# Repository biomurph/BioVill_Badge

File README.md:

# BioVill_Badge
DEFCON Micro Fluidics Badge Design For Biohacking Village

## Features Lifted From [OpenDrop](https://github.com/GaudiLabs/OpenDrop)V2
* Arduino Micro
* HV507 64 bit high voltage SIPO
* OLED display 
* Feedback circuit 
* Two pushbutton switches
* Joystick
* Speaker
* Various LEDs
* Various test points

## Power Supply	
Most important change from OpenDrop is the power supply. This board is asking to be plugged into the mains. Super important to isolate the grounds. Pay attention.

### Low voltage power supply sharing ground with USB 

* 5VDC supplied by USB connection to computer or battery on Vin
* 3V3 supplied by the Arduino Micro
		
### High voltage power supply sharing ground with high voltage input

* High voltage in to HV507

### High voltate input specs

* 110VAC <> 240VAC 50Hz <> 60Hz

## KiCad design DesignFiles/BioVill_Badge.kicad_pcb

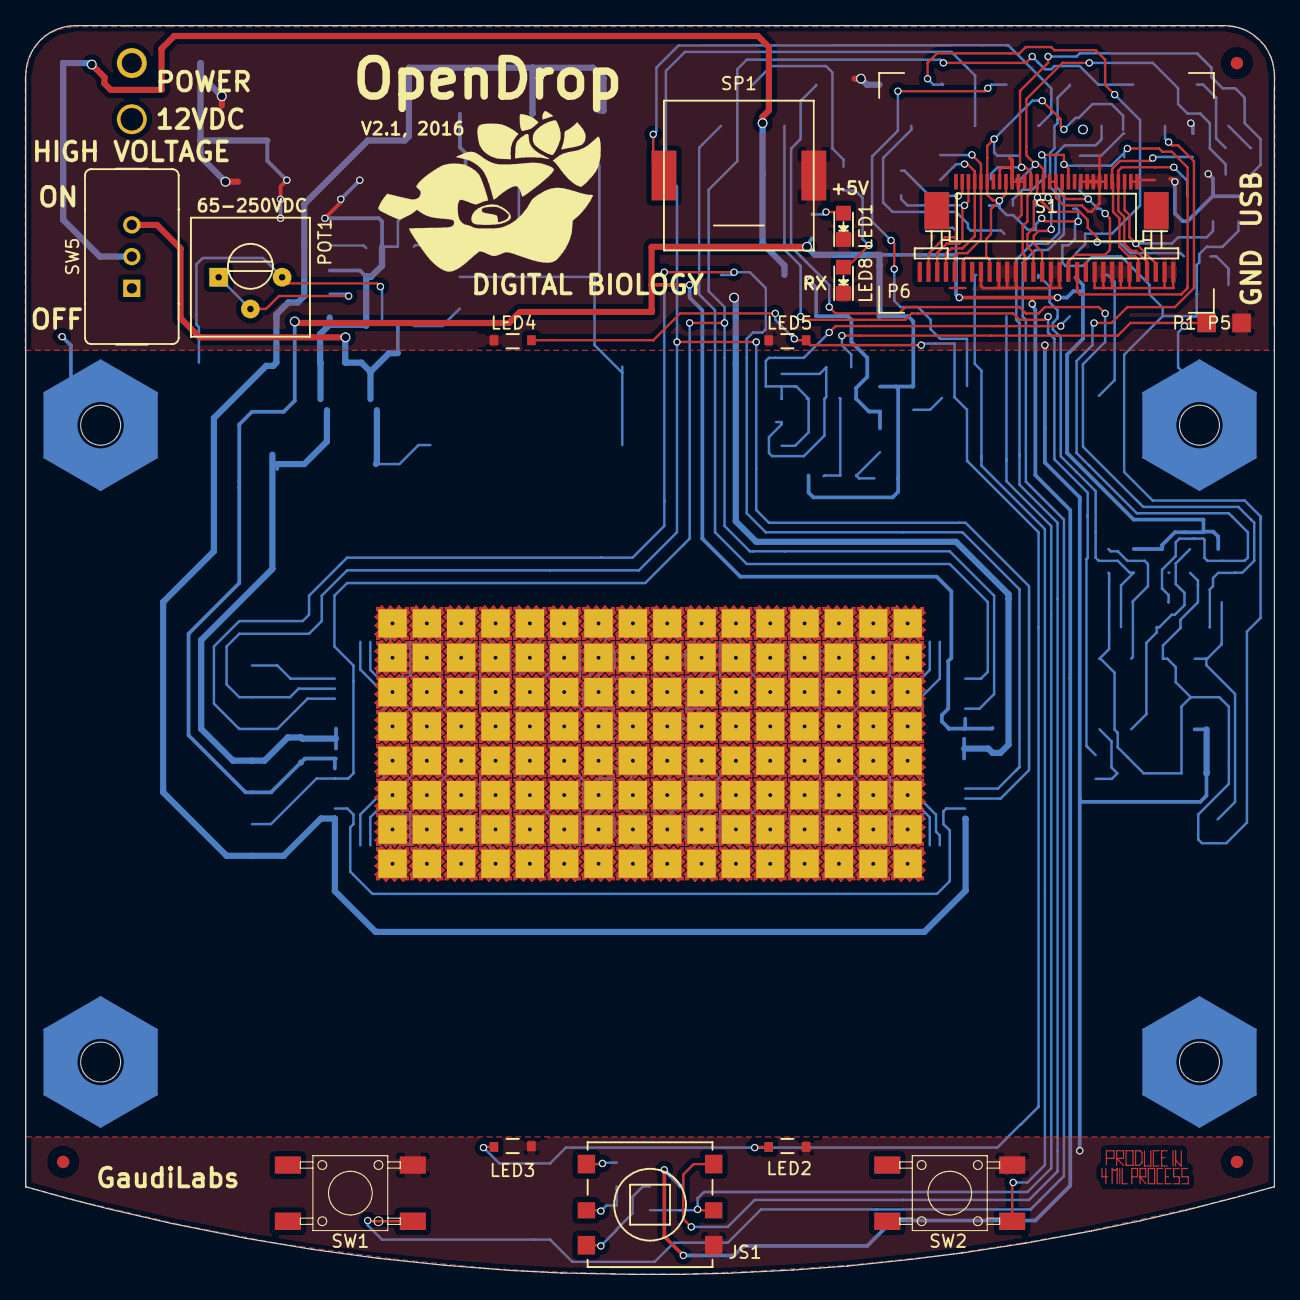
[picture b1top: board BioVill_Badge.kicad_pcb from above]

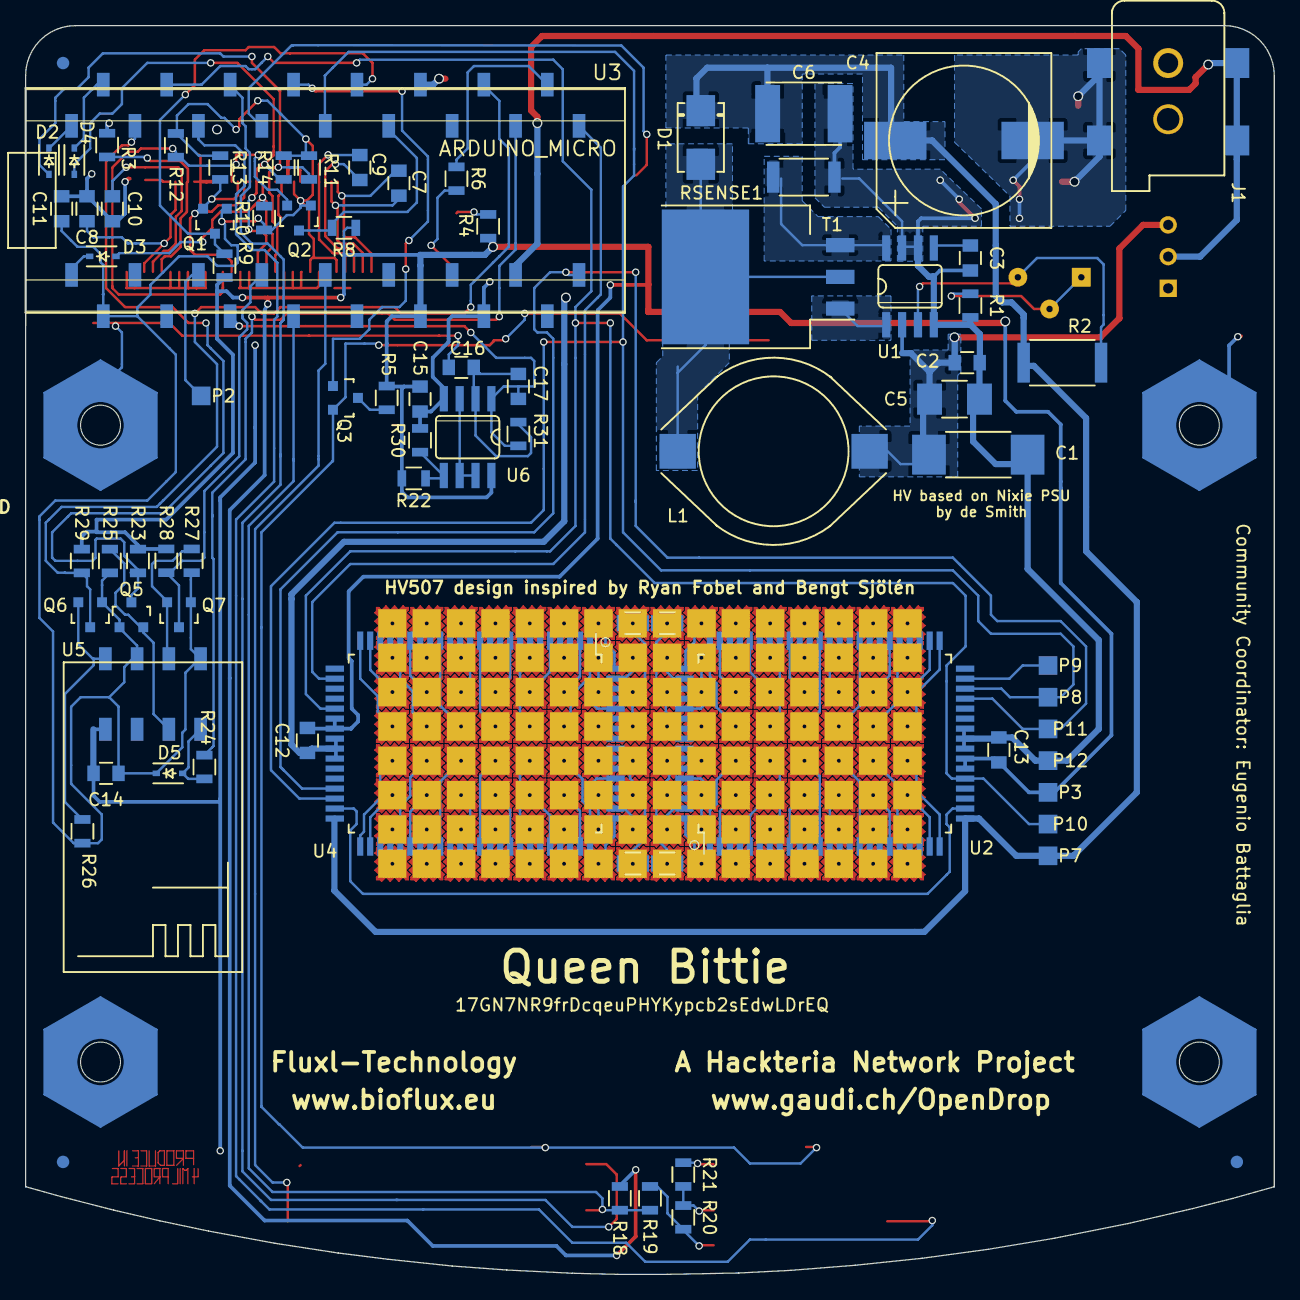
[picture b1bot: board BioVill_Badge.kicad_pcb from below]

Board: 2 copper layers, 100.0 x 100.0 mm, 225 parts (77 on the bottom side), 191 nets.

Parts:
C1: 100uF, 35V; R_2512_HandSoldering
C2, C3, C11, C12, C13, C14: 100nF; C_0805
C4: 4u7, 250V; C_SMD_12mm
C5: 10uF, 25V; C_1210_HandSoldering
C6: 100nF, 250V; C100n_250V
C7, C9, C15, C16: 1uF; C_0805
C8, C10: 2.2uF; C_0805
C17: 1pF; C_0805
D1: ES2F; DO-214AA
D2, D3, D4, D5: 1N4148; SOD-323
FLUXL1, FLUXL2, FLUXL3, FLUXL4, FLUXL5, FLUXL6, FLUXL7, FLUXL8, FLUXL9, FLUXL10, FLUXL11, FLUXL12, FLUXL13, FLUXL14, FLUXL15, FLUXL16, FLUXL17, FLUXL18, FLUXL19, FLUXL20, FLUXL21, FLUXL22, FLUXL23, FLUXL24, FLUXL25, FLUXL26, FLUXL27, FLUXL28, FLUXL29, FLUXL30, FLUXL31, FLUXL32, FLUXL33, FLUXL34, FLUXL35, FLUXL36, FLUXL37, FLUXL38, FLUXL39, FLUXL40, FLUXL41, FLUXL42, FLUXL43, FLUXL44, FLUXL45, FLUXL46, FLUXL47, FLUXL48, FLUXL49, FLUXL50, FLUXL51, FLUXL52, FLUXL53, FLUXL54, FLUXL55, FLUXL56, FLUXL57, FLUXL58, FLUXL59, FLUXL60, FLUXL61, FLUXL62, FLUXL63, FLUXL64, FLUXL65, FLUXL66, FLUXL67, FLUXL68, FLUXL69, FLUXL70, FLUXL71, FLUXL72, FLUXL73, FLUXL74, FLUXL75, FLUXL76, FLUXL77, FLUXL78, FLUXL79, FLUXL80, FLUXL81, FLUXL82, FLUXL83, FLUXL84, FLUXL85, FLUXL86, FLUXL87, FLUXL88, FLUXL89, FLUXL90, FLUXL91, FLUXL92, FLUXL93, FLUXL94, FLUXL95, FLUXL96, FLUXL97, FLUXL98, FLUXL99, FLUXL100, FLUXL101, FLUXL102, FLUXL103, FLUXL104, FLUXL105, FLUXL106, FLUXL107, FLUXL108, FLUXL109, FLUXL110, FLUXL111, FLUXL112, FLUXL113, FLUXL114, FLUXL115, FLUXL116, FLUXL117, FLUXL118, FLUXL119, FLUXL120, FLUXL121, FLUXL122, FLUXL123, FLUXL124, FLUXL125, FLUXL126, FLUXL127, FLUXL128: FX; FLUXPAD_2_75_4MIL_4_5
J1: DC_JACK; DC_JACK_SMD
JS1: JoystickSMD; JoystickSMD_SKQUSeries
L1: 100uH; Inductor_18.54x15.24
LED1, LED8: LED; LED-0805
LED2, LED3, LED4, LED5: LED; LED_SIDE
P1, P2, P3, P5, P7, P8, P9, P10, P11, P12: CONN_01X01; Measurement_Point_Square-SMD-Pad_Small
P6: CONN_01X30; OLED_SolderPads
P13, P13#2, P13#3, P13#4: ScrewPad1; MountingHolePad_3x9mm
POT1: 5k Ohm; Potentiometer_Trimmer-Suntan-TSR-3386P
Q1, Q2, Q3, Q5, Q6, Q7: BSS138; SOT-23
R1: 8k; R_0805
R2: 1M5; R_2512
R3: 390k; R_0805
R4, R6: 390; R_0805
R5: 10; R_0805
R7, R15, R16, R17: 10k; R_0805_HeatPad
R8, R9, R10, R11, R12, R13, R14, R18, R19, R20, R21, R22, R23, R24, R25, R26, R27, R28, R29, R30, R31: 10k; R_0805
RSENSE1: 0R050; R_2010
S1: OLED_DISPLAY; OLED_096_1
SP1: SPEAKER; SMD_PA12_Piezzo
SW1, SW2: SW_PUSH; PUSH_BUTTON_SMD
SW5: SPST; Switch_On-On
T1: IRF 840S; D2PAK
U1: MAX1771ESA; SO08
U2, U4: HV507; PQFP-80_14x20mm_Pitch0.8mm
U3: ARDUINO_MICRO; ARDUINO_MICRO_SMD
U5: ESP8266_SMD
U6: MCP6002; SO08

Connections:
3.3V: C11.1, C14.1, D5.1, P6.6, P6.9, Q1.1, Q2.1, Q5.1, Q6.1, Q7.1, R10.1, R11.1, R12.1, R13.1, R14.1, R25.2, R26.2, R27.2, S1.6, S1.9, U3.19, U5.4, U5.8
+5V: C12.1, C13.1, C15.1, P3.1, R4.1, R5.2, R8.1, R9.1, R18.2, R22.1, R23.2, R28.2, R29.2, U2.30, U2.31, U3.29, U4.30, U4.31, U6.8
BL: P10.1, U2.29, U3.14, U4.29
CLK: P11.1, U2.37, U3.34, U4.37
DI: U3.1, U4.26
DIO_B: P9.1, U2.39
DISP_CS: D2.1, U3.17
DISP_DC: D4.1, U3.16
DISP_RES: D3.1, U3.18
DISP_SCL: Q1.3, R9.2, U3.8
DISP_SDA: Q2.3, R8.2, U3.7
ESP_GPIO0: Q5.3, R23.1, U3.15
ESP_RESET: Q7.3, R28.1, U3.24
ESP_RX: R24.1, U3.3
ESP_TX: Q6.3, R29.1, U3.4
FEEDBACK: C17.1, R31.1, U3.23, U6.1
GND: C1.2, C2.2, C3.2, C4.2, C5.2, C6.2, C8.2, C10.2, C11.2, C12.2, C13.2, C14.2, C15.2, J1.1, J1.2, JS1.4, LED1.1, LED2.1, LED3.1, LED4.1, LED5.1, LED8.1, P5.1, P6.8, P6.10, P6.11, P6.12, P6.16, P6.17, P6.21, P6.22, P6.23, P6.24, P6.25, P6.29, P6.30, P12.1, R1.2, R3.2, R30.2, RSENSE1.2, S1.8, S1.10, S1.11, S1.12, S1.16, S1.17, S1.21, S1.22, S1.23, S1.24, S1.25, S1.29, S1.30, SP1.1, SW1.2, SW2.2, U1.4, U1.6, U1.7, U2.32, U2.33, U2.34, U3.6, U3.31, U4.32, U4.33, U4.34, U5.1, U6.4
JOY: JS1.5, R18.1, R19.2, U3.25
LE: P8.1, U2.38, U3.9, U4.38
LED_LIGHT: Q3.1, U3.10
unnamed: C1.1, C2.1, C5.1, L1.1, SW5.1, U1.2
unnamed: C3.1, U1.5
unnamed: C7.1, P6.2, S1.2
unnamed: C7.2, P6.3, S1.3
unnamed: C8.1, P6.28, S1.28
unnamed: C9.1, P6.4, S1.4
unnamed: C9.2, P6.5, S1.5
unnamed: C10.1, P6.27, S1.27
unnamed: C16.1, C17.2, R31.2, U6.2
unnamed: D1.2, L1.2, T1.2
unnamed: D2.2, P6.13, R11.2, S1.13
unnamed: D3.2, P6.14, R10.2, S1.14
unnamed: D4.2, P6.15, R14.2, S1.15
unnamed: D5.2, R24.2, U5.7
unnamed: FLUXL1.1, U2.44
unnamed: FLUXL2.1, U2.47
unnamed: FLUXL3.1, U2.51
unnamed: FLUXL4.1, U2.54
unnamed: FLUXL5.1, U2.58
unnamed: FLUXL6.1, U2.61
unnamed: FLUXL7.1, U2.65
unnamed: FLUXL8.1, U2.70
unnamed: FLUXL9.1, U2.43
unnamed: FLUXL10.1, U2.48
unnamed: FLUXL11.1, U2.50
unnamed: FLUXL12.1, U2.55
unnamed: FLUXL13.1, U2.59
unnamed: FLUXL14.1, U2.62
unnamed: FLUXL15.1, U2.69
unnamed: FLUXL16.1, U2.66
unnamed: FLUXL17.1, U2.42
unnamed: FLUXL18.1, U2.46
unnamed: FLUXL19.1, U2.52
unnamed: FLUXL20.1, U2.56
unnamed: FLUXL21.1, U2.60
unnamed: FLUXL22.1, U2.63
unnamed: FLUXL23.1, U2.68
unnamed: FLUXL24.1, U2.67
unnamed: FLUXL25.1, U2.41
unnamed: FLUXL26.1, U2.45
unnamed: FLUXL27.1, U2.49
unnamed: FLUXL28.1, U2.53
unnamed: FLUXL29.1, U2.57
unnamed: FLUXL30.1, U2.64
unnamed: FLUXL31.1, U2.72
unnamed: FLUXL32.1, U2.71
unnamed: FLUXL33.1, U2.24
unnamed: FLUXL34.1, U2.20
unnamed: FLUXL35.1, U2.16
unnamed: FLUXL36.1, U2.12
unnamed: FLUXL37.1, U2.8
unnamed: FLUXL38.1, U2.1
unnamed: FLUXL39.1, U2.73
unnamed: FLUXL40.1, U2.74
unnamed: FLUXL41.1, U2.23
unnamed: FLUXL42.1, U2.19
unnamed: FLUXL43.1, U2.13
unnamed: FLUXL44.1, U2.9
unnamed: FLUXL45.1, U2.5
unnamed: FLUXL46.1, U2.2
unnamed: FLUXL47.1, U2.78
unnamed: FLUXL48.1, U2.77
unnamed: FLUXL49.1, U2.22
unnamed: FLUXL50.1, U2.17
unnamed: FLUXL51.1, U2.15
unnamed: FLUXL52.1, U2.10
unnamed: FLUXL53.1, U2.6
unnamed: FLUXL54.1, U2.3
unnamed: FLUXL55.1, U2.76
unnamed: FLUXL56.1, U2.79
unnamed: FLUXL57.1, U2.21
unnamed: FLUXL58.1, U2.18
unnamed: FLUXL59.1, U2.14
unnamed: FLUXL60.1, U2.11
unnamed: FLUXL61.1, U2.7
unnamed: FLUXL62.1, U2.4
unnamed: FLUXL63.1, U2.80
unnamed: FLUXL64.1, U2.75
unnamed: FLUXL65.1, U4.41
unnamed: FLUXL66.1, U4.42
unnamed: FLUXL67.1, U4.43
unnamed: FLUXL68.1, U4.44
unnamed: FLUXL69.1, U4.45
unnamed: FLUXL70.1, U4.46
unnamed: FLUXL71.1, U4.47
unnamed: FLUXL72.1, U4.48
unnamed: FLUXL73.1, U4.49
unnamed: FLUXL74.1, U4.50
unnamed: FLUXL75.1, U4.51
unnamed: FLUXL76.1, U4.52
unnamed: FLUXL77.1, U4.53
unnamed: FLUXL78.1, U4.54
unnamed: FLUXL79.1, U4.55
unnamed: FLUXL80.1, U4.56
unnamed: FLUXL81.1, U4.57
unnamed: FLUXL82.1, U4.58
unnamed: FLUXL83.1, U4.59
unnamed: FLUXL84.1, U4.60
unnamed: FLUXL85.1, U4.61
unnamed: FLUXL86.1, U4.62
unnamed: FLUXL87.1, U4.63
unnamed: FLUXL88.1, U4.64
unnamed: FLUXL89.1, U4.65
unnamed: FLUXL90.1, U4.66
unnamed: FLUXL91.1, U4.67
unnamed: FLUXL92.1, U4.68
unnamed: FLUXL93.1, U4.69
unnamed: FLUXL94.1, U4.70
unnamed: FLUXL95.1, U4.71
unnamed: FLUXL96.1, U4.72
unnamed: FLUXL97.1, U4.73
unnamed: FLUXL98.1, U4.74
unnamed: FLUXL99.1, U4.75
unnamed: FLUXL100.1, U4.76
unnamed: FLUXL101.1, U4.77
unnamed: FLUXL102.1, U4.78
unnamed: FLUXL103.1, U4.79
unnamed: FLUXL104.1, U4.80
unnamed: FLUXL105.1, U4.1
unnamed: FLUXL106.1, U4.2
unnamed: FLUXL107.1, U4.3
unnamed: FLUXL108.1, U4.4
unnamed: FLUXL109.1, U4.5
unnamed: FLUXL110.1, U4.6
unnamed: FLUXL111.1, U4.7
unnamed: FLUXL112.1, U4.8
unnamed: FLUXL113.1, U4.9
unnamed: FLUXL114.1, U4.10
unnamed: FLUXL115.1, U4.11
unnamed: FLUXL116.1, U4.12
unnamed: FLUXL117.1, U4.13
unnamed: FLUXL118.1, U4.14
unnamed: FLUXL119.1, U4.15
unnamed: FLUXL120.1, U4.16
unnamed: FLUXL121.1, U4.17
unnamed: FLUXL122.1, U4.18
unnamed: FLUXL123.1, U4.19
unnamed: FLUXL124.1, U4.20
unnamed: FLUXL125.1, U4.21
unnamed: FLUXL126.1, U4.22
unnamed: FLUXL127.1, U4.23
unnamed: FLUXL128.1, U4.24
unnamed: JS1.1, R21.1
unnamed: JS1.2, R20.1, R21.2
unnamed: JS1.3, R19.1, R20.2
unnamed: LED1.2, R4.2
unnamed: LED2.2, LED3.2, LED4.2, LED5.2, Q3.2
unnamed: LED8.2, R6.2
unnamed: P2.1, U3.22
unnamed: P6.18, Q1.2, R13.2, S1.18
unnamed: P6.19, Q2.2, R12.2, S1.19
unnamed: P6.26, R3.1, S1.26
unnamed: POT1.1, POT1.2, R1.1
unnamed: POT1.3, R2.2, U1.3
unnamed: Q3.3, R5.1
unnamed: Q5.2, R25.1, U5.5
unnamed: Q6.2, R26.1, U5.2
unnamed: Q7.2, R27.1, U5.6
unnamed: R22.2, R30.1, U6.5
unnamed: RSENSE1.1, T1.3, U1.8
unnamed: T1.1, U1.1
unnamed: U2.26, U4.39
unnamed: U6.3, U6.6, U6.7
RX_LED: R6.1, U3.2
SPK: SP1.2, U3.11
SW1: SW1.1, U3.13
SW2: SW2.1, U3.26
SW3: JS1.6, U3.12
VIN: J1.3, SW5.2, U3.32
V_GND: C16.2, P1.1
V_HV: C4.1, C6.1, D1.1, P7.1, R2.1, U2.25, U4.40

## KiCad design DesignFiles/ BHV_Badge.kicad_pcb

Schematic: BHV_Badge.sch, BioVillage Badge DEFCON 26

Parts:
C1: 100uF, 35V; R_2512_HandSoldering
C2, C3, C12, C13, C14, C22, C26, C30, C33, C34, C36: 100nF; C_0805
C4, C18: 4u7, 250V; c_elec_10x10
C5, C21: 22uF; C_1206
C6, C35: 100nF, 250V; C_1206_HandSoldering
C7, C9, C11, C15, C16, C20, C24, C27: 1uF; C_0805
C8, C10: 2.2uF; C_0805
C17: 1pF; C_0805
C19: 22uF, 50V; c_elec_6.3x5.8
C23, C25: 22pF; C_0805
C28, C29: 3.3nF; C_0805
C31: 220nF; C_0805
C32: 100uF,50V; R_2512_HandSoldering
D1: ES2F; DO-214AA
D2, D3: 1N4148; D_SOD-323
FLUXL_1_1, FLUXL_1_8, FLUXL_16_1, FLUXL_16_8: FX; FLUXPAD_2_75_4MIL_4_5_res3
FLUXL_1_2, FLUXL_1_7, FLUXL_16_2, FLUXL_16_7: FX; FLUXPAD_2_75_4MIL_4_5_res1
FLUXL_1_3, FLUXL_1_6, FLUXL_16_3, FLUXL_16_6: FX; FLUXPAD_2_75_4MIL_4_5_res2
FLUXL_1_4, FLUXL_1_5, FLUXL_16_4, FLUXL_16_5: FX; FLUXPAD_2_75_4MIL_4_5_res4
FLUXL_1_4b1, FLUXL_1_5b1, FLUXL_16_4b1, FLUXL_16_5b1: FX; FLUXPAD_2_75_4MIL_4_5_res5
FLUXL_2_1, FLUXL_15_8: FX; FLUXPAD_2_75_4MIL_4_5_topleft
FLUXL_2_2, FLUXL_2_7, FLUXL_3_2, FLUXL_3_3, FLUXL_3_4, FLUXL_3_5, FLUXL_3_6, FLUXL_3_7, FLUXL_4_2, FLUXL_4_3, FLUXL_4_4, FLUXL_4_5, FLUXL_4_6, FLUXL_4_7, FLUXL_5_2, FLUXL_5_3, FLUXL_5_4, FLUXL_5_5, FLUXL_5_6, FLUXL_5_7, FLUXL_6_2, FLUXL_6_3, FLUXL_6_4, FLUXL_6_5, FLUXL_6_6, FLUXL_6_7, FLUXL_7_2, FLUXL_7_3, FLUXL_7_4, FLUXL_7_5, FLUXL_7_6, FLUXL_7_7, FLUXL_8_2, FLUXL_8_3, FLUXL_8_4, FLUXL_8_5, FLUXL_8_6, FLUXL_8_7, FLUXL_9_2, FLUXL_9_3, FLUXL_9_4, FLUXL_9_5, FLUXL_9_6, FLUXL_9_7, FLUXL_10_2, FLUXL_10_3, FLUXL_10_4, FLUXL_10_5, FLUXL_10_6, FLUXL_10_7, FLUXL_11_2, FLUXL_11_3, FLUXL_11_4, FLUXL_11_5, FLUXL_11_6, FLUXL_11_7, FLUXL_12_2, FLUXL_12_3, FLUXL_12_4, FLUXL_12_5, FLUXL_12_6, FLUXL_12_7, FLUXL_13_2, FLUXL_13_3, FLUXL_13_4, FLUXL_13_5, FLUXL_13_6, FLUXL_13_7, FLUXL_14_2, FLUXL_14_3, FLUXL_14_4, FLUXL_14_5, FLUXL_14_6, FLUXL_14_7, FLUXL_15_2, FLUXL_15_7: FX; FLUXPAD_2_75_4MIL_4_5
FLUXL_2_3, FLUXL_2_4, FLUXL_2_5, FLUXL_2_6, FLUXL_15_3, FLUXL_15_4, FLUXL_15_5, FLUXL_15_6: FX; FLUXPAD_2_75_4MIL_4_5_side
FLUXL_2_8, FLUXL_15_1: FX; FLUXPAD_2_75_4MIL_4_5_topright
FLUXL_3_1, FLUXL_3_8, FLUXL_4_1, FLUXL_4_8, FLUXL_5_1, FLUXL_5_8, FLUXL_6_1, FLUXL_6_8, FLUXL_7_1, FLUXL_7_8, FLUXL_8_1, FLUXL_8_8, FLUXL_9_1, FLUXL_9_8, FLUXL_10_1, FLUXL_10_8, FLUXL_11_1, FLUXL_11_8, FLUXL_12_1, FLUXL_12_8, FLUXL_13_1, FLUXL_13_8, FLUXL_14_1, FLUXL_14_8: FX; FLUXPAD_2_75_4MIL_4_5_top
J1: USB_C_Receptacle; USB_C_Receptacle_Amphenol_12401610E4-2A
J2: Conn_02x05_Odd_Even; Pin_Header_Straight_2x05_Pitch1.27mm_SMD
JS1: JoystickSMD; 5P_Joystick_SKRHAAE010
L1: 100uH; SRN1060
LED1, LED2, LED3: LED; LED-0805
P1, P3, P7, P8, P9, P10, P11, P12: CONN_01X01; Measurement_Point_Square-SMD-Pad_Small
P2: ScrewPad4; Measurement_Point_Croki
P4: CONN_PSEUDO_AC; Measurement_Point_Square-SMD-Pad_Small
P13: ScrewPad1; MountingHolePad_3x9mm
P14: ScrewPad2; MountingHolePad_3x9mm
P15: ScrewPad3; MountingHolePad_3x9mm
P16: ScrewPad4; MountingHolePad_3x9mm
R1: 6.8k; R_0805
R2: 1M5; R_2512
R3, R9: 390k; R_0805
R4, R6, R8, R13: 390; R_0805
R5, R10, R18, R19, R20, R21, R22, R30, R44: 10k; R_0805
R7, R15, R16, R17: 10R; R_0805_HeatPad
R11: 47k; R_0805
R12, R33, R35, R38, R39, R42, R43: 2.2k; R_0805
R14, R23: 5R1; R_0805_HeatPad
R31: 15k; R_0805
R32, R34, R36, R37, R40, R41, R45, R48, R49, R51: 220; R_0805
RSENSE1: 0R1; R_2010
S1: OLED_DISPLAY; OLED_096_1_Flip
SP1: SPEAKER; Speaker16mm
SW1, SW2: SW_PUSH; PUSH_BUTTON_SMD
SW3: PTS810_SJK_250_SMTR_LFS; PTS810
SW5: DPDT; OS202011MA2QS1_DPDT
T1: TK560P60Y; D-Pak_TO252AA
U1: MAX1771ESA; SO08
U2, U4: HV507; PQFP-80_14x20mm_Pitch0.8mm
U3: PAM8301; SOT-23-6
U5: SAMD21G18B-A changed from SAML21; TQFP-48_7x7mm_Pitch0.5mm
U6: MCP6002; SO08
U7, U8, U9: HCPL0534; HCPL_Optocoupler_SMD
U10, U11, U12, U13: AQY210EH; SMD_DIP4
U14: TLV1117-33; SOT-223
U15: MCP41010; SO08
U16: 74xx14; SOIC-14_N
Y1: 32.765; Crystal_SMD_3215-2pin_3.2x1.5mm

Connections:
AC: C31.1, U5.7
AREF: C24.2, U5.4
BL: R40.2, U5.12
BL_C: P10.1, R42.1, U2.29 (BL), U4.29 (BL), U8.6
CLK: R32.2, U5.20
CLK_C: P11.1, R33.1, U2.37 (CLK), U4.37 (CLK), U7.7
D13: R8.1, U5.26
D+: J1.A6, J1.B6, U5.34
D-: J1.A7, J1.B7, U5.33
DI: R34.2, U5.19
DIO_B: P9.1, U2.39 (DIO_B)
DISP_CS: S1.13 (CS), U5.21
DISP_DC: S1.15 (D/C#_SA0), U5.16
DISP_RES: S1.14 (RES), U5.24
DISP_SCL: S1.18 (D0_(SCL)), U5.32
DISP_SDA: S1.19 (D1_(SA)), U5.31
DI_C: R35.1, U4.26 (DIO_A), U9.7
FEEDBACK: C17.1, R31.1, U5.8, U6.1
GND: C1.2, C2.2, C3.2, C4.2, C5.2, C6.2, C8.2, C10.2, C14.2, C15.2, C20.2, C21.2, C22.1, C23.1, C24.1, C25.1, C26.2, C27.1, C28.1, C29.1, C30.2, C32.2, C33.1, C34.1, J1.A1, J1.A12, J1.B1, J1.B12, J1.S1, J2.3, J2.5, J2.9, JS1.5 (D_(rigth)), JS1.7, JS1.8, LED1.1 (K), LED2.1 (K), LED3.1 (K), P2.1, P13.1, R1.2, R3.2, R13.2, R14.2, R23.2, R30.2, RSENSE1.2, S1.8 (VSS), S1.10 (BS0), S1.11 (BS1), S1.12 (BS2), S1.16 (R/W#), S1.17 (E/RD#), S1.21 (D8), S1.22 (D4), S1.23 (D5), S1.24 (D6), S1.25 (D7), S1.29 (SDA), S1.30 (NC_(GND)), SW1.2, SW2.2, SW3.3, SW3.4, SW5.7, SW5.8, U1.4, U1.6, U1.7, U3.2, U5.5, U5.18, U5.35, U5.42, U6.4 (V-), U7.2, U7.3, U8.2, U8.3, U9.2, U9.3, U10.3, U12.3, U14.1, U15.4, U16.7
GND_C: C12.2, C13.2, C18.2, C19.2, C35.2, C36.2, P12.1, U2.32 (DIR), U2.33 (GND), U2.34 (HVGND), U4.32 (DIR), U4.33 (GND), U4.34 (HVGND), U7.5, U8.5, U9.5, U12.4
LE: R37.2, U5.13
LE_C: P8.1, R39.1, U2.38 (LE), U4.38 (LE), U7.6
unnamed: C1.1, C2.1, L1.1, SW5.1, SW5.4, U1.2
unnamed: C3.1, U1.5
unnamed: C7.1, S1.2 (C2P)
unnamed: C7.2, S1.3 (C2N)
unnamed: C8.1, S1.28 (VCC)
unnamed: C9.1, S1.4 (C1P)
unnamed: C9.2, S1.5 (C1N)
unnamed: C10.1, S1.27 (VCOMH)
unnamed: C11.1, R12.1, R13.1
unnamed: C11.2, U3.3
unnamed: C16.1, C17.2, R31.2, U6.2 (-)
unnamed: C20.1, U5.43
unnamed: C23.2, U5.1, Y1.1
unnamed: C25.2, U5.2, Y1.2
unnamed: C28.2, D2.2, R10.2, U16.13
unnamed: C29.2, D3.1, R44.2, U16.9
unnamed: C31.2, R11.1, U16.3
unnamed: D1.2, L1.2, T1.2
unnamed: D2.1, D3.2, R10.1, R44.1, U16.4
unnamed: FLUXL_1_1.1, U2.41 (HV_OUT_1)
unnamed: FLUXL_1_2.1, U2.44 (HV_OUT_4)
unnamed: FLUXL_1_3.1, U2.42 (HV_OUT_2)
unnamed: FLUXL_1_4.1, FLUXL_1_4b1.1, P4.1, U2.43 (HV_OUT_3)
unnamed: FLUXL_1_5.1, FLUXL_1_5b1.1, U2.22 (HV_OUT_62)
unnamed: FLUXL_1_6.1, U2.23 (HV_OUT_63)
unnamed: FLUXL_1_7.1, U2.21 (HV_OUT_61)
unnamed: FLUXL_1_8.1, U2.24 (HV_OUT_64)
unnamed: FLUXL_2_1.1, U2.47 (HV_OUT_7)
unnamed: FLUXL_2_2.1, U2.48 (HV_OUT_8)
unnamed: FLUXL_2_3.1, U2.46 (HV_OUT_6)
unnamed: FLUXL_2_4.1, U2.45 (HV_OUT_5)
unnamed: FLUXL_2_5.1, U2.20 (HV_OUT_60)
unnamed: FLUXL_2_6.1, U2.19 (HV_OUT_59)
unnamed: FLUXL_2_7.1, U2.17 (HV_OUT_57)
unnamed: FLUXL_2_8.1, U2.18 (HV_OUT_58)
unnamed: FLUXL_3_1.1, U2.51 (HV_OUT_11)
unnamed: FLUXL_3_2.1, U2.50 (HV_OUT_10)
unnamed: FLUXL_3_3.1, U2.52 (HV_OUT_12)
unnamed: FLUXL_3_4.1, U2.49 (HV_OUT_9)
unnamed: FLUXL_3_5.1, U2.16 (HV_OUT_56)
unnamed: FLUXL_3_6.1, U2.13 (HV_OUT_53)
unnamed: FLUXL_3_7.1, U2.15 (HV_OUT_55)
unnamed: FLUXL_3_8.1, U2.14 (HV_OUT_54)
unnamed: FLUXL_4_1.1, U2.54 (HV_OUT_14)
unnamed: FLUXL_4_2.1, U2.55 (HV_OUT_15)
unnamed: FLUXL_4_3.1, U2.56 (HV_OUT_16)
unnamed: FLUXL_4_4.1, U2.53 (HV_OUT_13)
unnamed: FLUXL_4_5.1, U2.12 (HV_OUT_52)
unnamed: FLUXL_4_6.1, U2.9 (HV_OUT_49)
unnamed: FLUXL_4_7.1, U2.10 (HV_OUT_50)
unnamed: FLUXL_4_8.1, U2.11 (HV_OUT_51)
unnamed: FLUXL_5_1.1, U2.58 (HV_OUT_18)
unnamed: FLUXL_5_2.1, U2.59 (HV_OUT_19)
unnamed: FLUXL_5_3.1, U2.60 (HV_OUT_20)
unnamed: FLUXL_5_4.1, U2.57 (HV_OUT_17)
unnamed: FLUXL_5_5.1, U2.8 (HV_OUT_48)
unnamed: FLUXL_5_6.1, U2.5 (HV_OUT_45)
unnamed: FLUXL_5_7.1, U2.6 (HV_OUT_46)
unnamed: FLUXL_5_8.1, U2.7 (HV_OUT_47)
unnamed: FLUXL_6_1.1, U2.61 (HV_OUT_21)
unnamed: FLUXL_6_2.1, U2.62 (HV_OUT_22)
unnamed: FLUXL_6_3.1, U2.63 (HV_OUT_23)
unnamed: FLUXL_6_4.1, U2.64 (HV_OUT_24)
unnamed: FLUXL_6_5.1, U2.1 (HV_OUT_41)
unnamed: FLUXL_6_6.1, U2.2 (HV_OUT_42)
unnamed: FLUXL_6_7.1, U2.3 (HV_OUT_43)
unnamed: FLUXL_6_8.1, U2.4 (HV_OUT_44)
unnamed: FLUXL_7_1.1, U2.65 (HV_OUT_25)
unnamed: FLUXL_7_2.1, U2.69 (HV_OUT_29)
unnamed: FLUXL_7_3.1, U2.68 (HV_OUT_28)
unnamed: FLUXL_7_4.1, U2.72 (HV_OUT_32)
unnamed: FLUXL_7_5.1, U2.73 (HV_OUT_33)
unnamed: FLUXL_7_6.1, U2.78 (HV_OUT_38)
unnamed: FLUXL_7_7.1, U2.76 (HV_OUT_36)
unnamed: FLUXL_7_8.1, U2.80 (HV_OUT_40)
unnamed: FLUXL_8_1.1, U2.70 (HV_OUT_30)
unnamed: FLUXL_8_2.1, U2.66 (HV_OUT_26)
unnamed: FLUXL_8_3.1, U2.67 (HV_OUT_27)
unnamed: FLUXL_8_4.1, U2.71 (HV_OUT_31)
unnamed: FLUXL_8_5.1, U2.74 (HV_OUT_34)
unnamed: FLUXL_8_6.1, U2.77 (HV_OUT_37)
unnamed: FLUXL_8_7.1, U2.79 (HV_OUT_39)
unnamed: FLUXL_8_8.1, U2.75 (HV_OUT_35)
unnamed: FLUXL_9_1.1, U4.75 (HV_OUT_35)
unnamed: FLUXL_9_2.1, U4.79 (HV_OUT_39)
unnamed: FLUXL_9_3.1, U4.77 (HV_OUT_37)
unnamed: FLUXL_9_4.1, U4.74 (HV_OUT_34)
unnamed: FLUXL_9_5.1, U4.71 (HV_OUT_31)
unnamed: FLUXL_9_6.1, U4.67 (HV_OUT_27)
unnamed: FLUXL_9_7.1, U4.66 (HV_OUT_26)
unnamed: FLUXL_9_8.1, U4.70 (HV_OUT_30)
unnamed: FLUXL_10_1.1, U4.80 (HV_OUT_40)
unnamed: FLUXL_10_2.1, U4.76 (HV_OUT_36)
unnamed: FLUXL_10_3.1, U4.78 (HV_OUT_38)
unnamed: FLUXL_10_4.1, U4.73 (HV_OUT_33)
unnamed: FLUXL_10_5.1, U4.72 (HV_OUT_32)
unnamed: FLUXL_10_6.1, U4.68 (HV_OUT_28)
unnamed: FLUXL_10_7.1, U4.69 (HV_OUT_29)
unnamed: FLUXL_10_8.1, U4.65 (HV_OUT_25)
unnamed: FLUXL_11_1.1, U4.4 (HV_OUT_44)
unnamed: FLUXL_11_2.1, U4.3 (HV_OUT_43)
unnamed: FLUXL_11_3.1, U4.2 (HV_OUT_42)
unnamed: FLUXL_11_4.1, U4.1 (HV_OUT_41)
unnamed: FLUXL_11_5.1, U4.64 (HV_OUT_24)
unnamed: FLUXL_11_6.1, U4.63 (HV_OUT_23)
unnamed: FLUXL_11_7.1, U4.62 (HV_OUT_22)
unnamed: FLUXL_11_8.1, U4.61 (HV_OUT_21)
unnamed: FLUXL_12_1.1, U4.7 (HV_OUT_47)
unnamed: FLUXL_12_2.1, U4.6 (HV_OUT_46)
unnamed: FLUXL_12_3.1, U4.5 (HV_OUT_45)
unnamed: FLUXL_12_4.1, U4.8 (HV_OUT_48)
unnamed: FLUXL_12_5.1, U4.57 (HV_OUT_17)
unnamed: FLUXL_12_6.1, U4.60 (HV_OUT_20)
unnamed: FLUXL_12_7.1, U4.59 (HV_OUT_19)
unnamed: FLUXL_12_8.1, U4.58 (HV_OUT_18)
unnamed: FLUXL_13_1.1, U4.11 (HV_OUT_51)
unnamed: FLUXL_13_2.1, U4.10 (HV_OUT_50)
unnamed: FLUXL_13_3.1, U4.9 (HV_OUT_49)
unnamed: FLUXL_13_4.1, U4.12 (HV_OUT_52)
unnamed: FLUXL_13_5.1, U4.53 (HV_OUT_13)
unnamed: FLUXL_13_6.1, U4.56 (HV_OUT_16)
unnamed: FLUXL_13_7.1, U4.55 (HV_OUT_15)
unnamed: FLUXL_13_8.1, U4.54 (HV_OUT_14)
unnamed: FLUXL_14_1.1, U4.14 (HV_OUT_54)
unnamed: FLUXL_14_2.1, U4.15 (HV_OUT_55)
unnamed: FLUXL_14_3.1, U4.13 (HV_OUT_53)
unnamed: FLUXL_14_4.1, U4.16 (HV_OUT_56)
unnamed: FLUXL_14_5.1, U4.49 (HV_OUT_9)
unnamed: FLUXL_14_6.1, U4.52 (HV_OUT_12)
unnamed: FLUXL_14_7.1, U4.50 (HV_OUT_10)
unnamed: FLUXL_14_8.1, U4.51 (HV_OUT_11)
unnamed: FLUXL_15_1.1, U4.18 (HV_OUT_58)
unnamed: FLUXL_15_2.1, U4.17 (HV_OUT_57)
unnamed: FLUXL_15_3.1, U4.19 (HV_OUT_59)
unnamed: FLUXL_15_4.1, U4.20 (HV_OUT_60)
unnamed: FLUXL_15_5.1, U4.45 (HV_OUT_5)
unnamed: FLUXL_15_6.1, U4.46 (HV_OUT_6)
unnamed: FLUXL_15_7.1, U4.48 (HV_OUT_8)
unnamed: FLUXL_15_8.1, U4.47 (HV_OUT_7)
unnamed: FLUXL_16_1.1, U4.24 (HV_OUT_64)
unnamed: FLUXL_16_2.1, U4.21 (HV_OUT_61)
unnamed: FLUXL_16_3.1, U4.23 (HV_OUT_63)
unnamed: FLUXL_16_4.1, FLUXL_16_4b1.1, U4.22 (HV_OUT_62)
unnamed: FLUXL_16_5.1, FLUXL_16_5b1.1, U4.43 (HV_OUT_3)
unnamed: FLUXL_16_6.1, U4.42 (HV_OUT_2)
unnamed: FLUXL_16_7.1, U4.44 (HV_OUT_4)
unnamed: FLUXL_16_8.1, U4.41 (HV_OUT_1)
unnamed: J1.A5, R23.1
unnamed: J1.B5, R14.1
unnamed: JS1.1 (A_(up)), R21.1
unnamed: JS1.3 (C_(down)), R20.1, R21.2
unnamed: LED1.2 (A), R6.2
unnamed: LED2.2 (A), R4.2
unnamed: LED3.2 (A), R8.2
unnamed: R1.1, R9.2, U15.7
unnamed: R2.2, U1.3, U15.5, U15.6
unnamed: R3.1, S1.26 (REF)
unnamed: R22.2, R30.1, U6.5 (+)
unnamed: R32.1, U7.1
unnamed: R34.1, U9.1
unnamed: R36.1, U8.1
unnamed: R37.1, U7.4
unnamed: R40.1, U8.4
unnamed: R41.1, U9.4
unnamed: R43.1, U9.6
unnamed: R45.1, U10.1
unnamed: R48.1, U11.1
unnamed: R49.1, U12.1
unnamed: R51.1, U13.1
unnamed: RSENSE1.1, T1.3, U1.8
unnamed: SP1.1, U3.1
unnamed: SP1.2, U3.6
unnamed: T1.1, U1.1
unnamed: U2.26 (DIO_A), U4.39 (DIO_B)
unnamed: U6.3 (+), U6.6 (-), U6.7
unnamed: U10.2, U16.12
unnamed: U11.2, U16.2
unnamed: U12.2, U16.10
unnamed: U13.2, U16.6
unnamed: U16.1, U16.5, U16.8, U16.11
POL: R36.2, U5.23
POL_C: R38.1, U2.30 (POL), U4.30 (POL), U8.7
RESET: J2.10, R5.1, SW3.1, SW3.2, U5.40
RX_LED: R6.1, U5.48
SENS_PAD: P16.1, U5.47
SPK: R12.2, U5.3
SW1: SW1.1, U5.11
SW2: SW2.1, U5.29
SW3: JS1.2 (B_(left)), U5.30
SWCLK: J2.4, U5.45
SWDIO: J2.2, U5.46
VDD_C: C12.1, C13.1, C19.1, C36.1, P3.1, R33.2, R35.2, R38.2, R39.2, R42.2, R43.2, U2.31 (VDD), U4.31 (VDD), U7.8, U8.8, U9.8, U13.3
VSENS: R9.1, U5.9
V_CS: U5.22, U15.1
V_GND: C16.2, P1.1, P14.1
V_HV: C4.1, C6.1, D1.1, R2.1, U11.4
V_HV_C: C18.1, C35.1, P7.1, U2.25 (VPP), U4.40 (VPP), U10.4, U11.3
V_SCK: U5.28, U15.2
V_SI: U5.25, U15.3
V_USB: C5.1, C27.2, C32.1, J1.A4, J1.A9, J1.B4, J1.B9, R45.2, R48.2, R49.2, R51.2, SW5.2, SW5.5, U3.4, U3.5, U13.4, U14.3, U16.14

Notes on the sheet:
65-260VDC
Display
AC SWITCHER
HIGH VOLTAGE BOOST CONVERTER
FEEDBACK AMPLIFIER
INTERFACE
HIGH VOLTAGE DRIVER
OPTO ISOLATORS
MICROCONTROLLER
OLED DISPLAY
D6 / changed
A0 / vout
changed
10k
D3 / changed
LED? MKR
A3 / A3? MKR
A4? MKR
D8 / A5? MKR
D9 / A6? MKR
D4 / SDA? MKR
SCL? MKR
D1 / PWM2? MKR
D0 / PWM3? MKR
D23 / PWM4? MKR
D24 / PWM5? MKR
22/ MOSI? MKR
? / SCK? MKR
D2 / DATA? MKR
MISO? MKR
MOSI? MKR / SERCOM 1
SCK? MKR / SERCOM1
D10 / USB_PAD4??? MKR / SERCOM1
MISO? MKR / SERCOM1
PAD6? MKR
D7 / PAD7? MKR
PAD7? MKR
PAD0? MKR
TX? MKR
RX? MKR

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
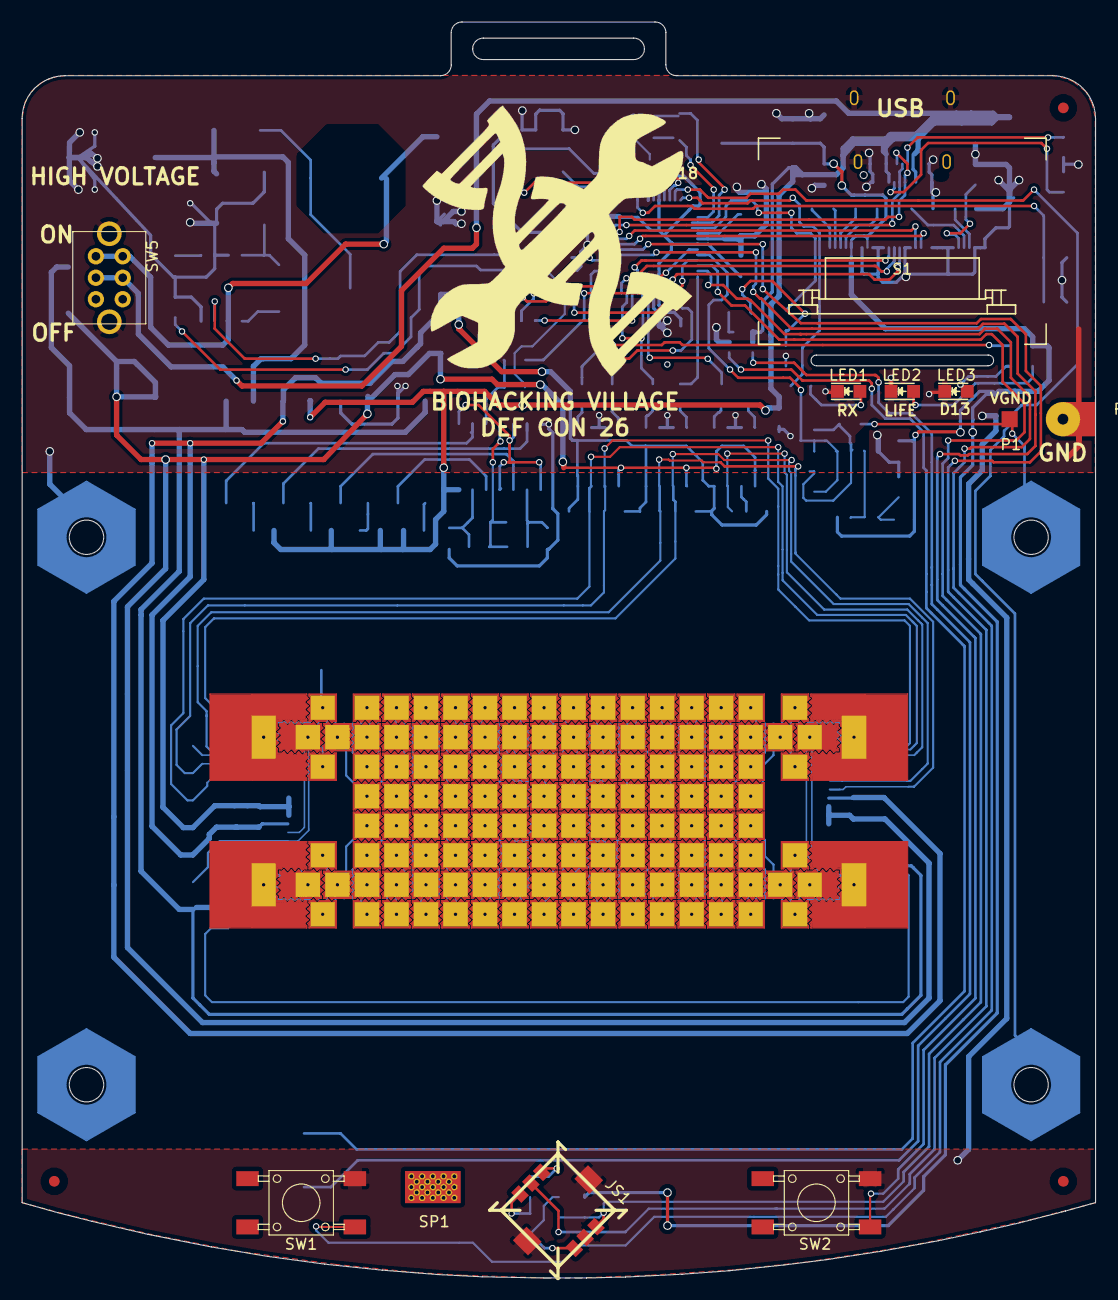
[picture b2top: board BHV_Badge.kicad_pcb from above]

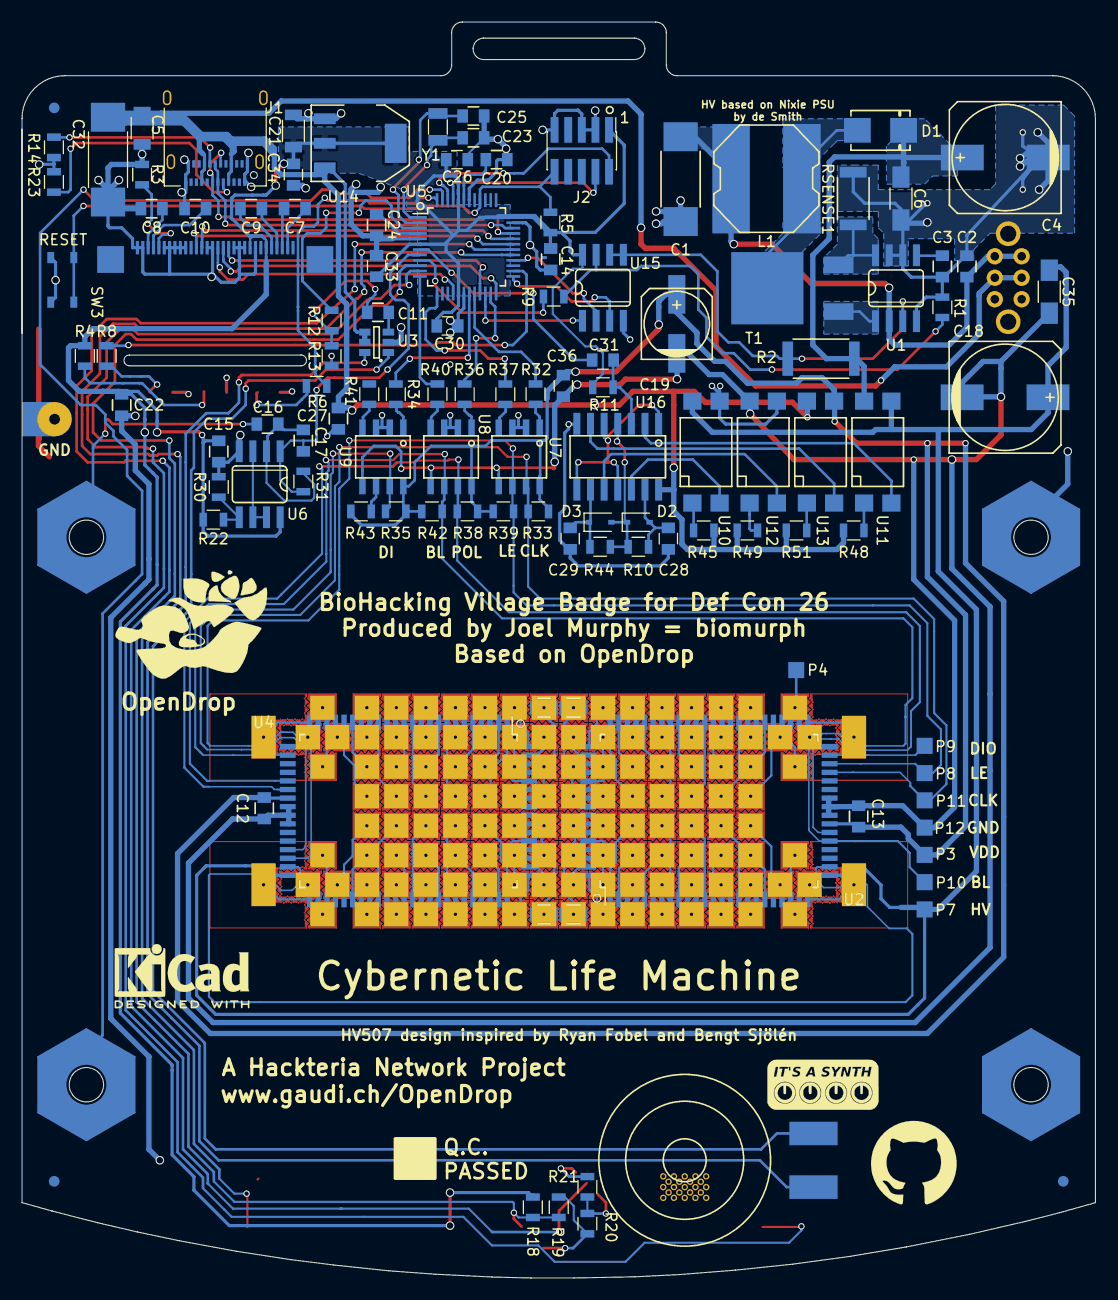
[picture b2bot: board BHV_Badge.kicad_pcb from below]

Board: 2 copper layers, 100.0 x 117.0 mm, 259 parts (112 on the bottom side), 225 nets.

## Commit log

2018-02-07 First Stab
2018-02-07 added sch pdf
2018-02-07 Moved sch pdf up a notch
2018-02-07 add link to readme
2018-02-26 updated parts and added bom draft
2018-02-26 minor changes
2018-02-27 removed openDrop library from list
2018-05-02 Moving files around to regenerate the core design
2019-03-06 Updated design to KiCAD version 5
    Tested
2019-03-06 updated USB connector
2019-03-06 reoved extraneous pro file
